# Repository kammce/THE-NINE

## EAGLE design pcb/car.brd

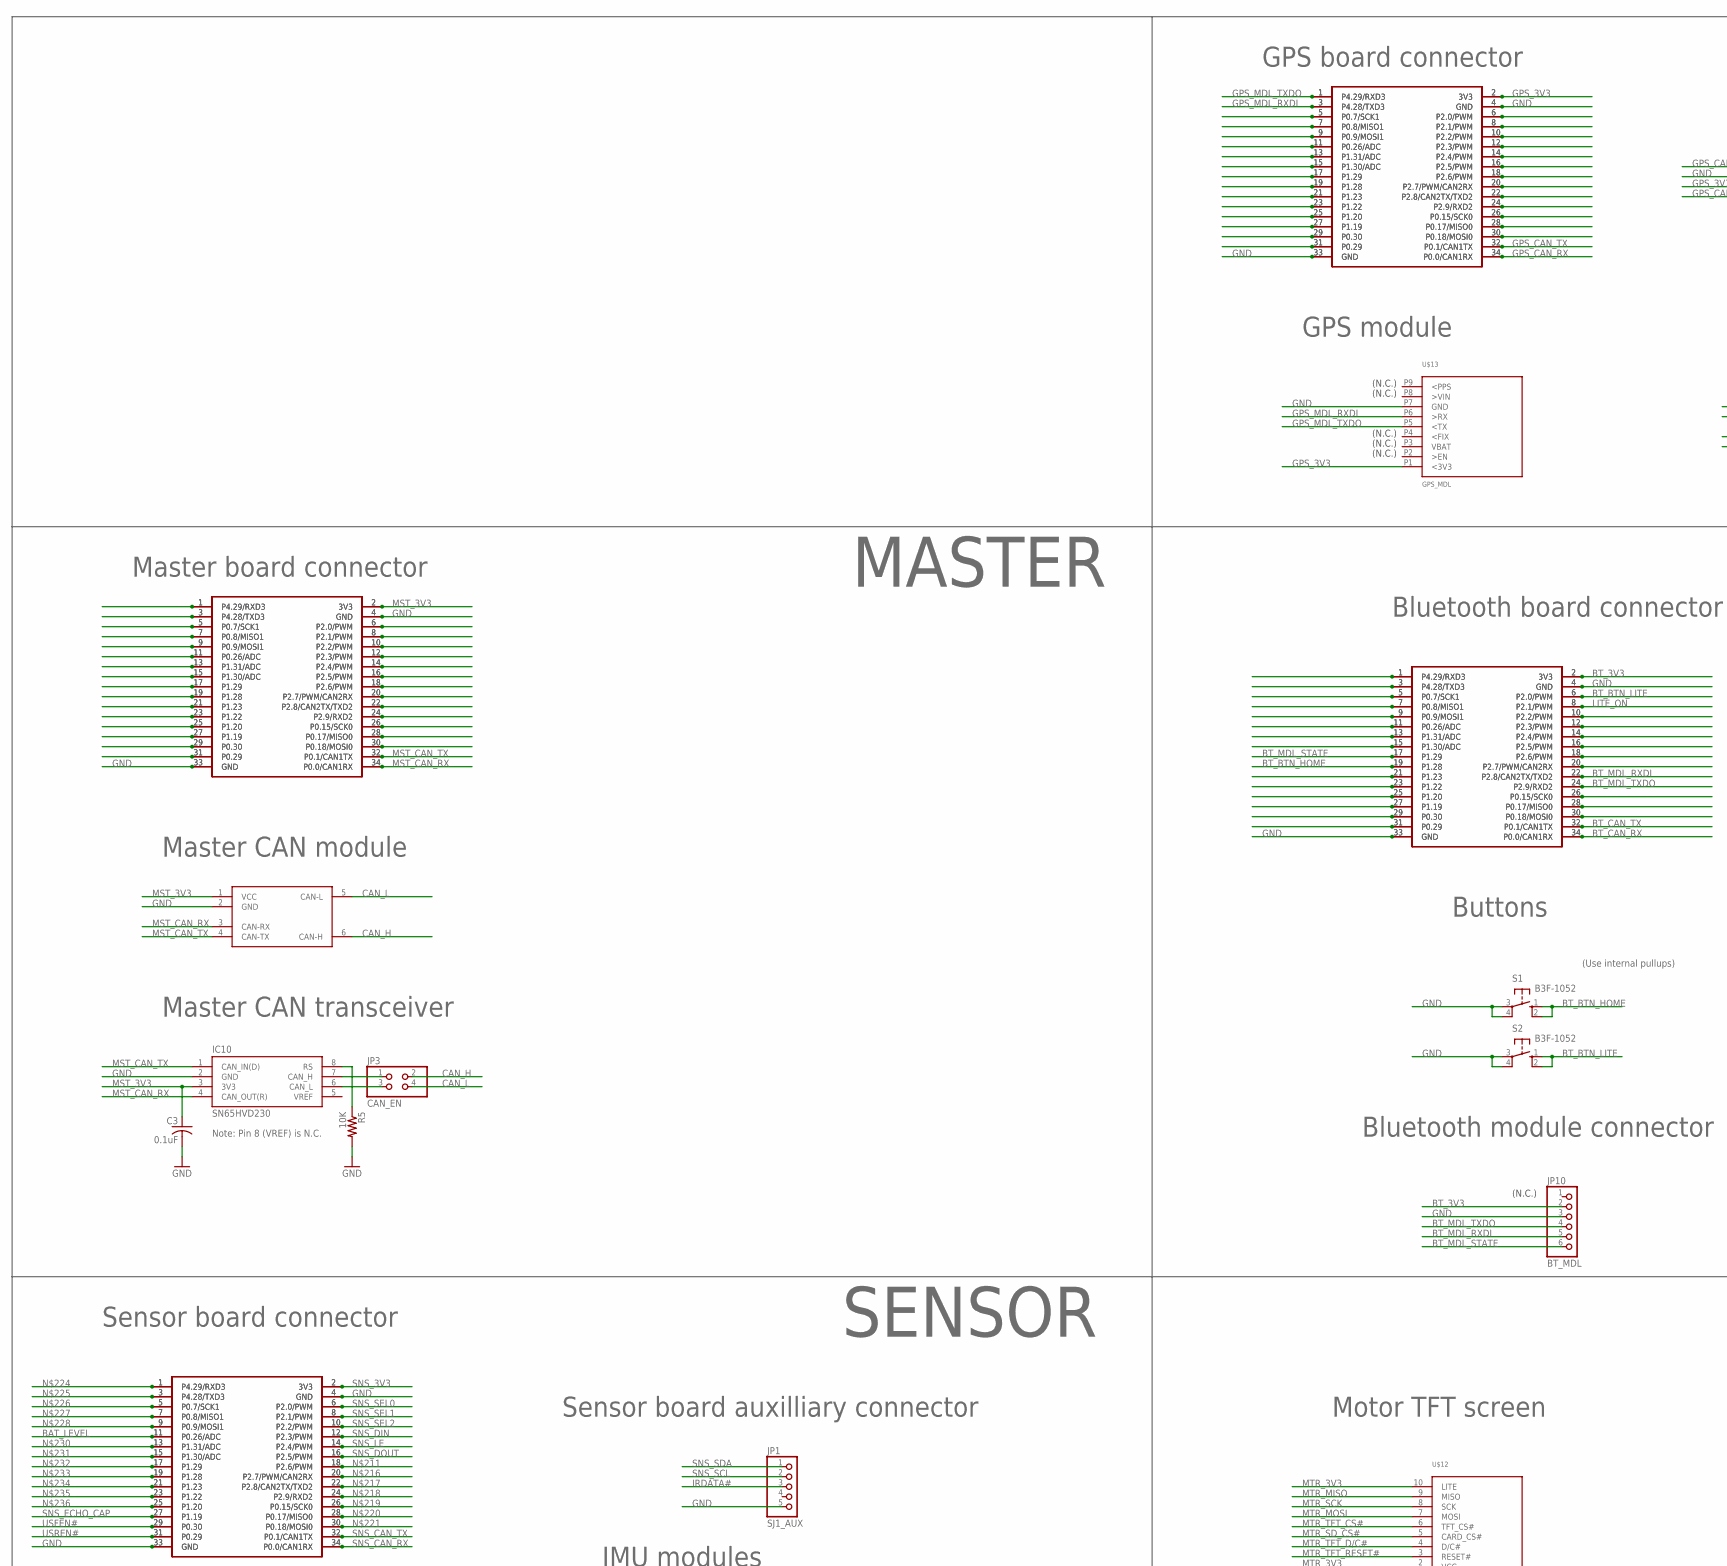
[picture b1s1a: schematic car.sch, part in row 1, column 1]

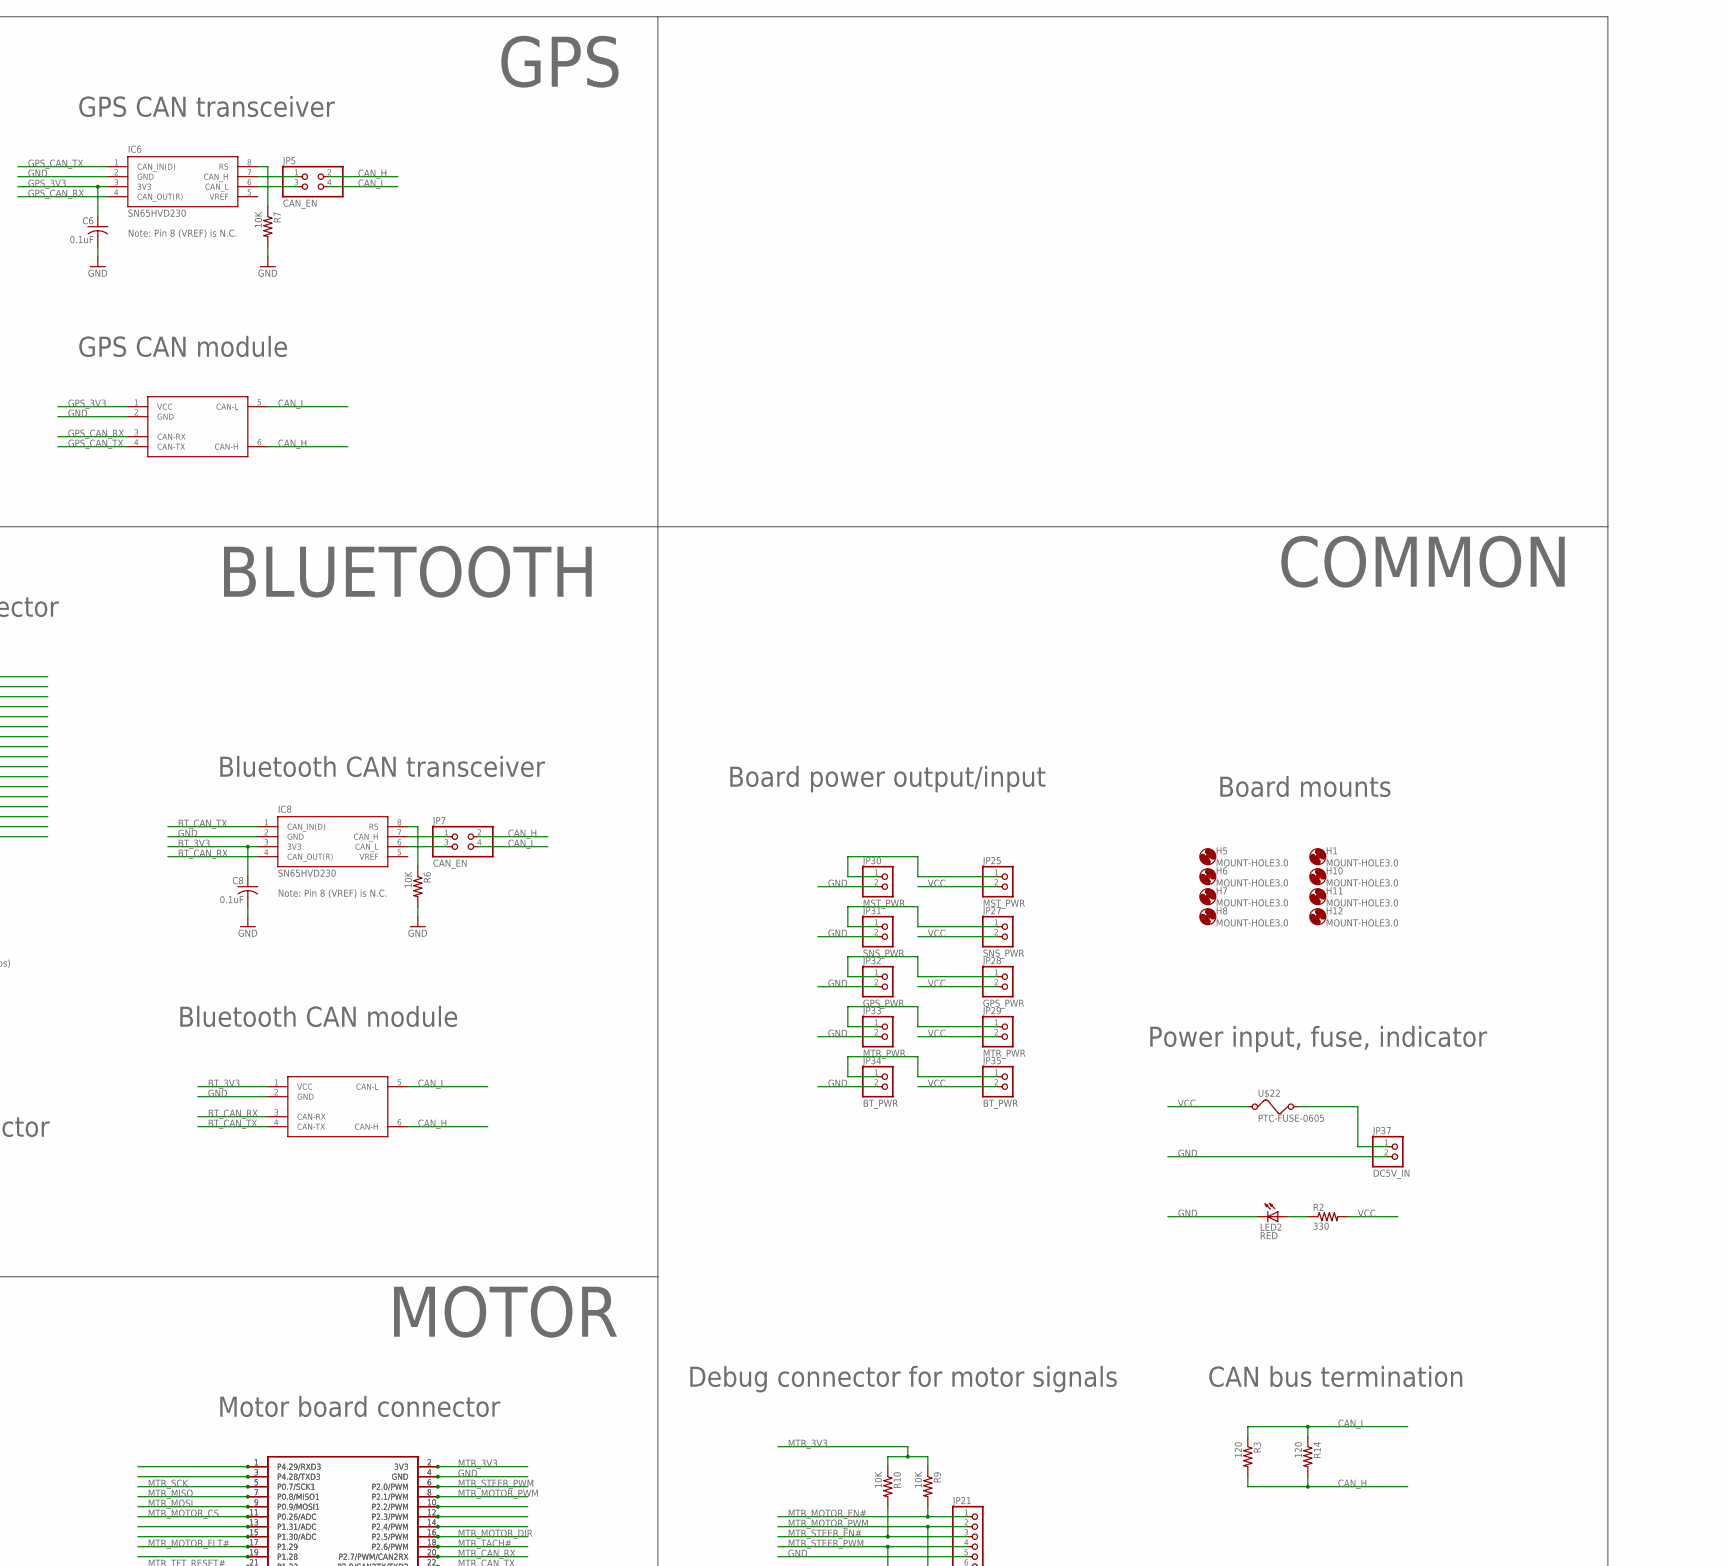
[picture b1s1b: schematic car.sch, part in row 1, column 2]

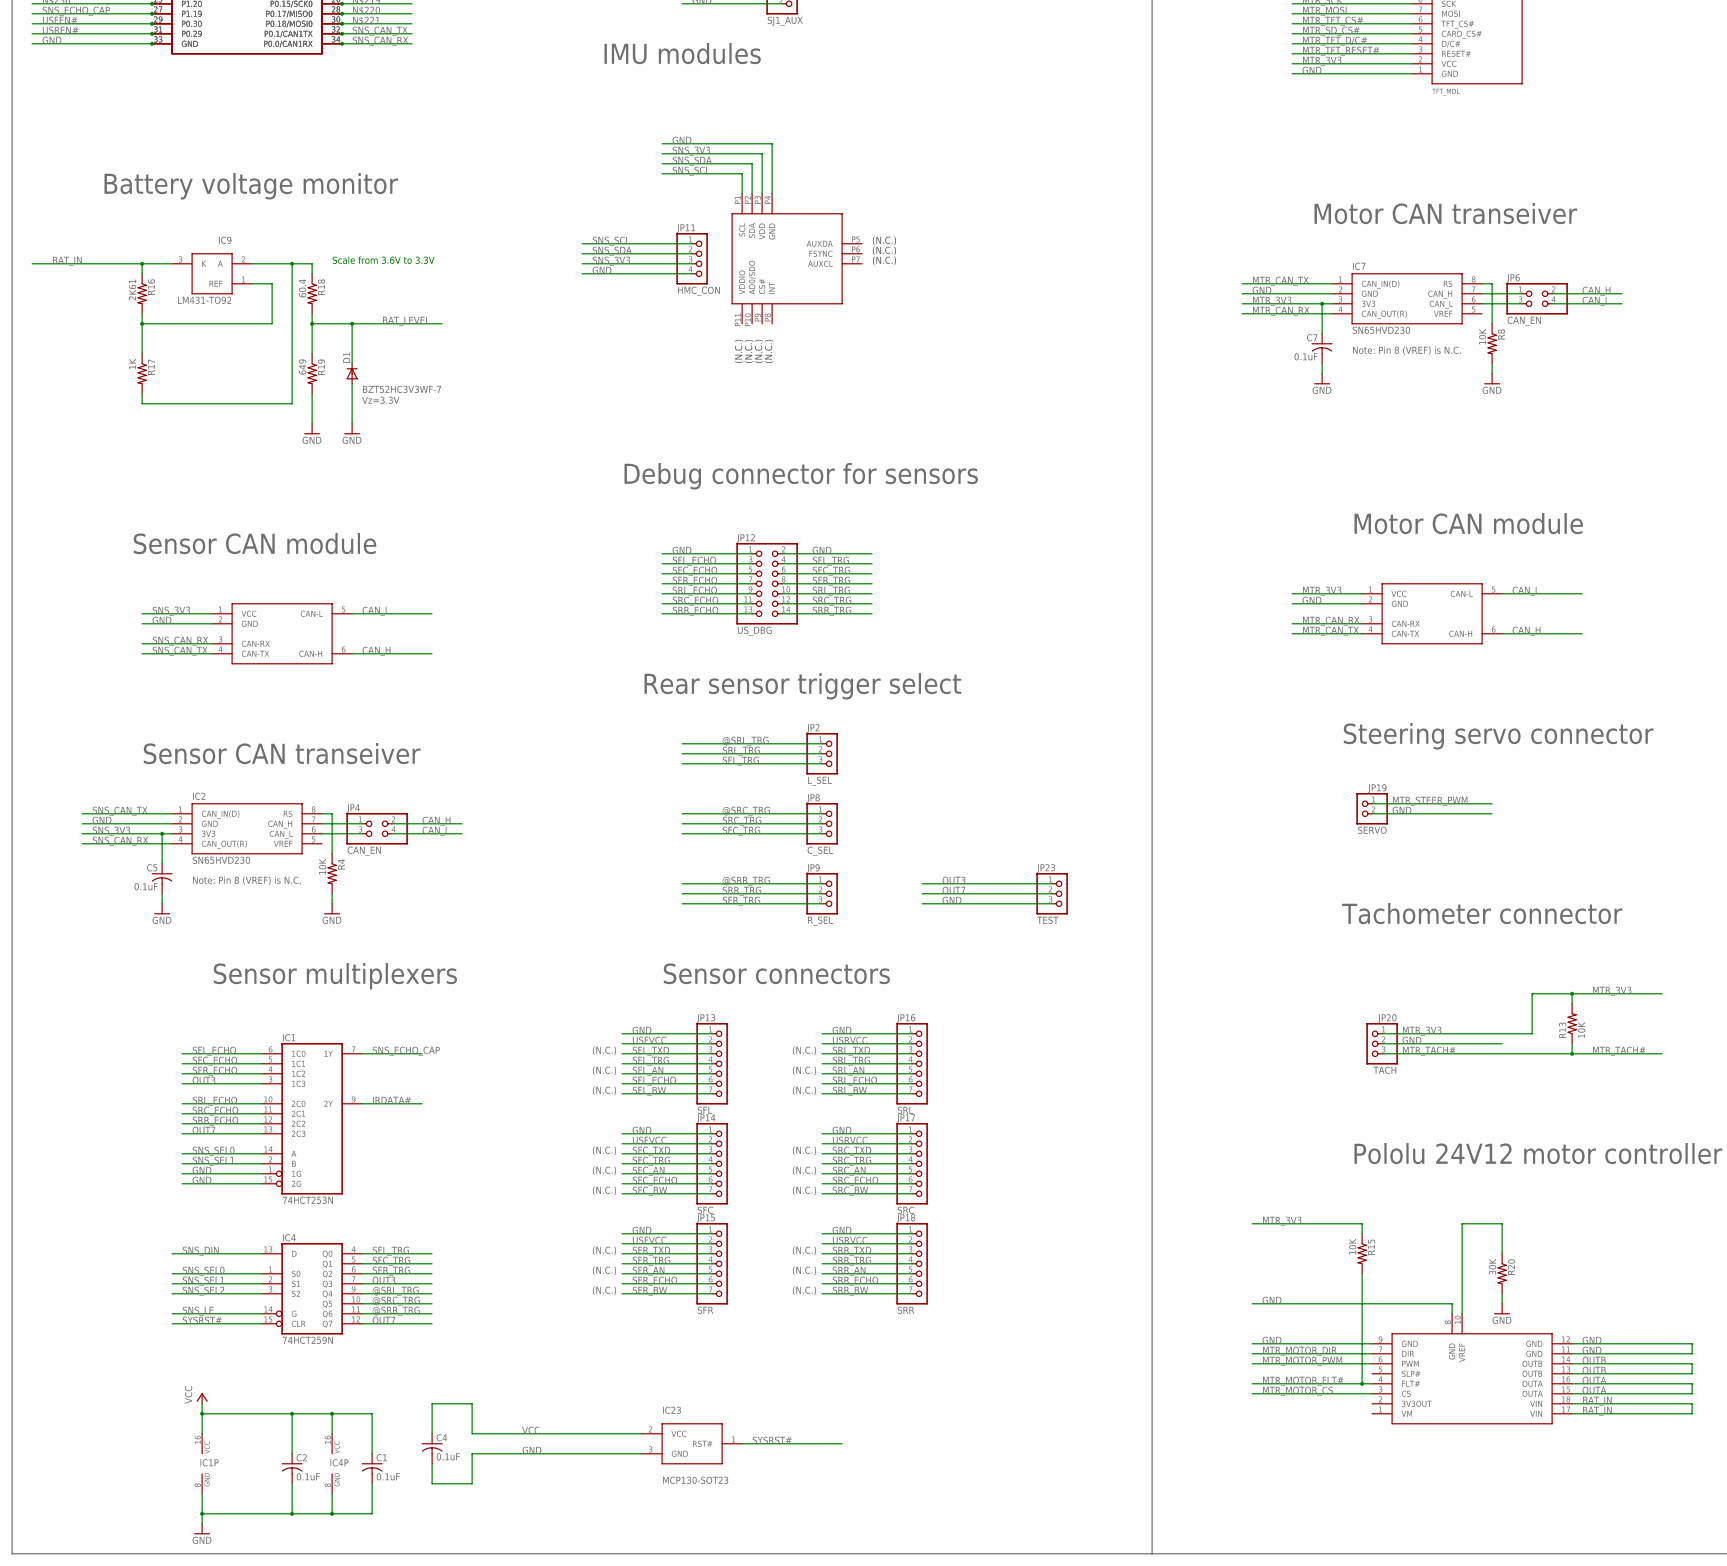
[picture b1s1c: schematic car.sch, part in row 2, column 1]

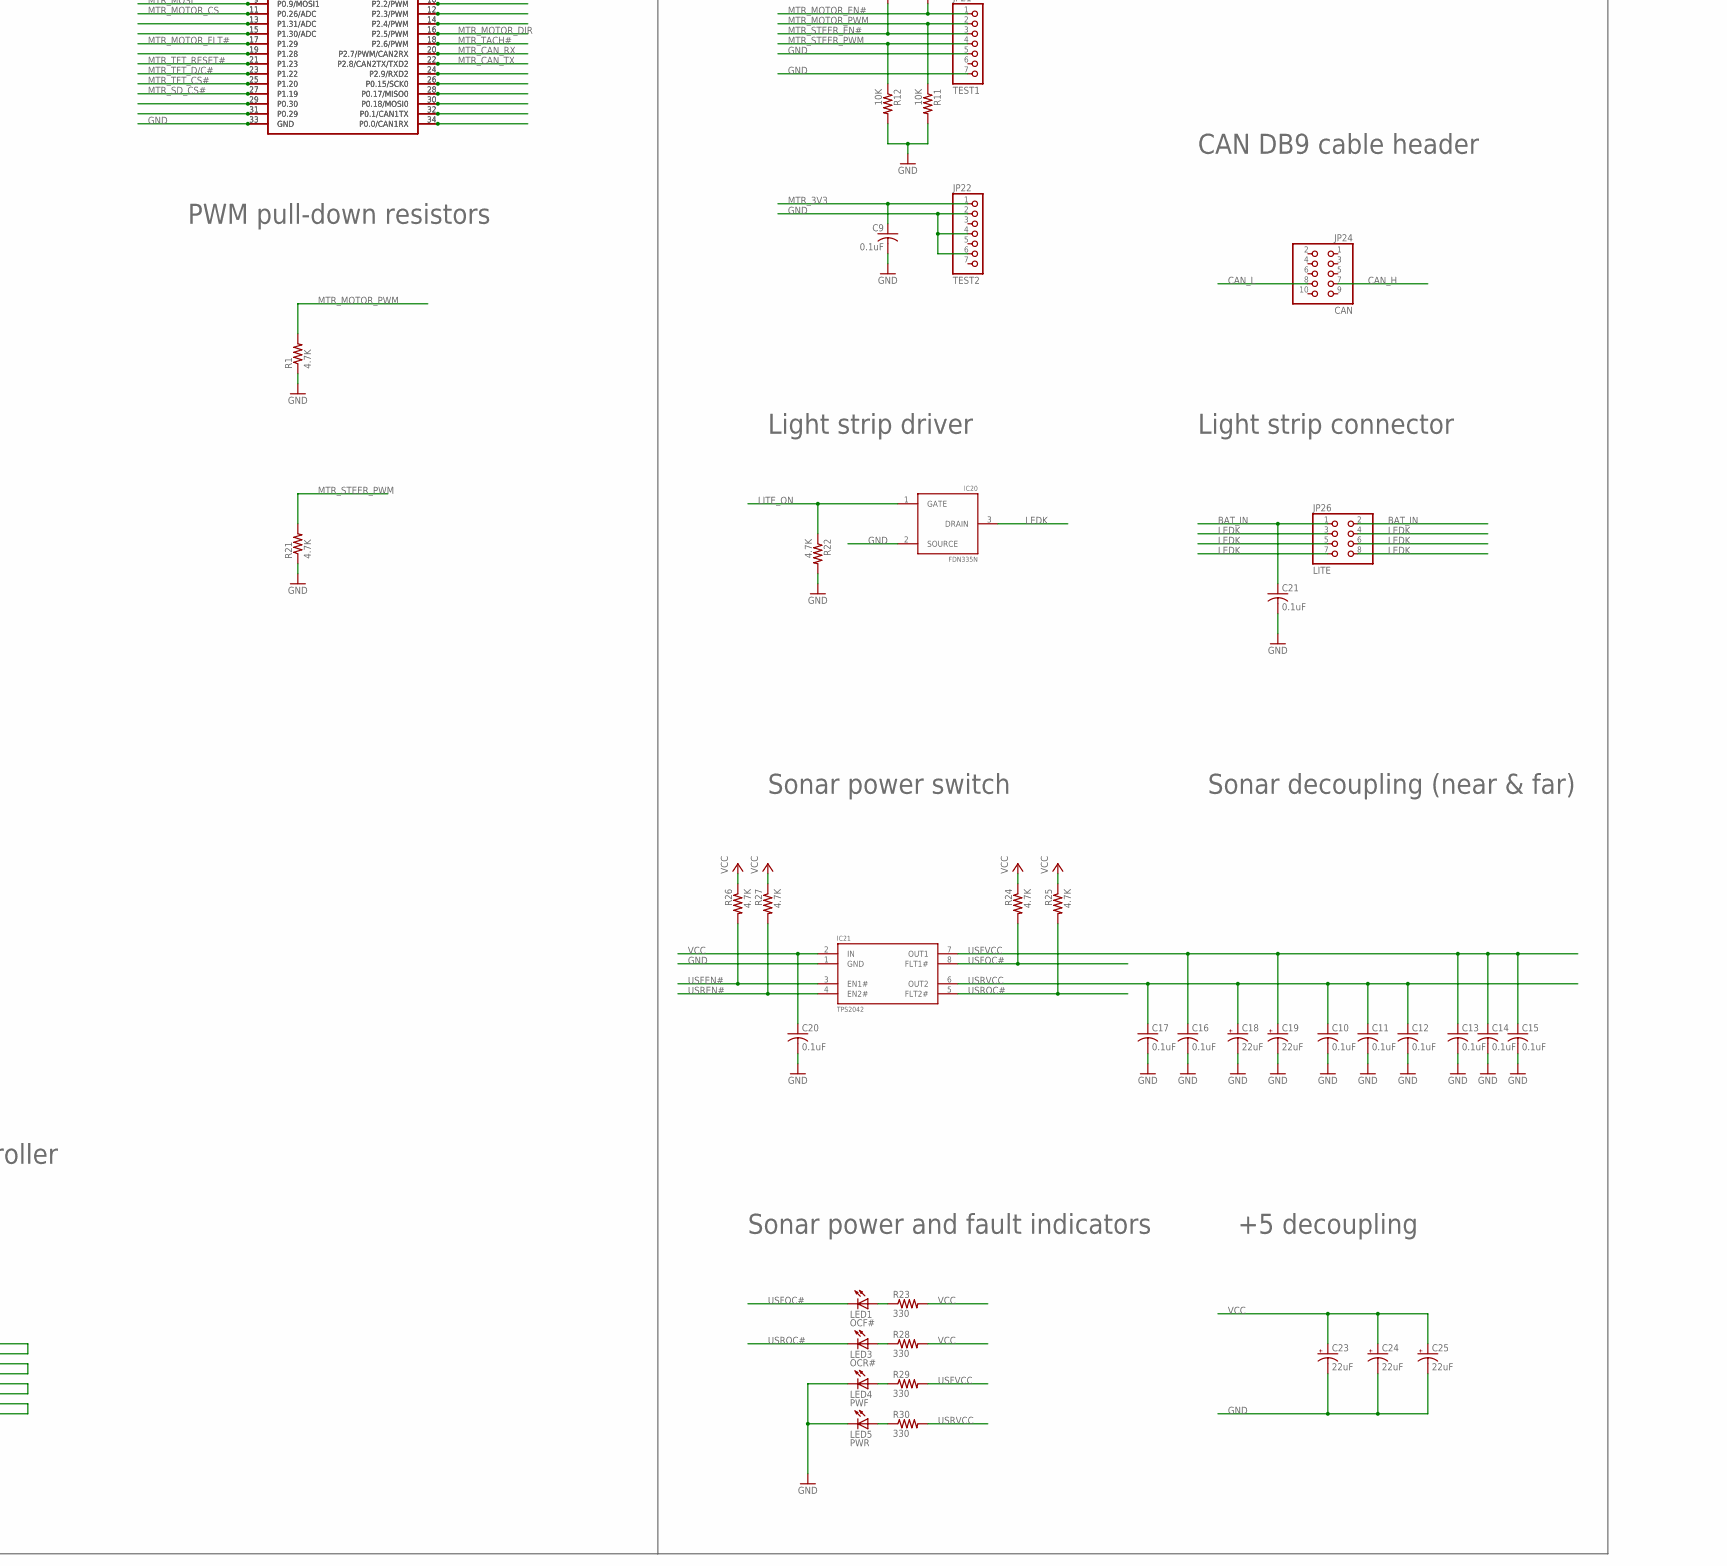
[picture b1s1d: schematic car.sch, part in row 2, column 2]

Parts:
C1, C2, C3, C4, C5, C6, C7, C8, C9, C10, C11, C12, C13, C14, C15, C16, C17, C20, C21: 0.1uF; C0603K
C18, C19, C23, C24, C25: 22uF; D/7343-31W
D1: BZT52HC3V3WF-7; SOD323-W
H1, H5, H6, H7, H8, H10, H11, H12: MOUNT-HOLE3.0; 3,0
IC1: 74HCT253N; DIL16
IC2, IC6, IC7, IC8, IC10: SN65HVD230; SOIC8
IC4: 74HCT259N; DIL16
IC9: LM431-TO92; TO-92
IC20: FDN335N; SOT23-3
IC21: TPS2042; SOIC8
IC22: 24V21
IC23: MCP130-SOT23; SOT23-3
IMU_MDL: MPU9250
JP1: SJ1_AUX; 1X05
JP2: L_SEL; 1X03
JP3, JP4, JP5, JP6, JP7: CAN_EN; 2X02
JP8: C_SEL; 1X03
JP9: R_SEL; 1X03
JP10: BT_MDL; 1X06
JP11: HMC_CON; 1X04
JP12: US_DBG; 2X07
JP13: SFL; 1X07
JP14: SFC; 1X07
JP15: SFR; 1X07
JP16: SRL; 1X07
JP17: SRC; 1X07
JP18: SRR; 1X07
JP19: SERVO; 1X02
JP20: TACH; 1X03
JP21: TEST1; 1X07
JP22: TEST2; 1X07
JP23: TEST; 1X03
JP24: CAN; 2X05
JP25, JP30: MST_PWR; 1X02
JP26: LITE; 2X04
JP27, JP31: SNS_PWR; 1X02
JP28, JP32: GPS_PWR; 1X02
JP29, JP33: MTR_PWR; 1X02
JP34, JP35: BT_PWR; 1X02
JP37: DC5V_IN; 1X02
LED1: OCF#; CHIPLED_0603
LED2: RED; CHIPLED_0603
LED3: OCR#; CHIPLED_0603
LED4: PWF; CHIPLED_0603
LED5: PWR; CHIPLED_0603
R1, R21, R22, R24, R25, R26, R27: 4.7K; R0603
R2, R23, R28, R29, R30: 330; R0603
R3, R14: 120; R0603
R4, R5, R6, R7, R8, R9, R10, R11, R12, R13, R15: 10K; R0603
R16: 2K61; R0603
R17: 1K; R0603
R18: 60.4; R0603
R19: 649; R0603
R20: 30K; R0603
S1, S2: B3F-1052; B3F-10XX
U$7, U$8, U$9, U$10, U$11: WAVESHARE-CAN
U$12: TFT_MDL; ADA-TFT
U$13: GPS_MDL; ADA-GPS
U$19, U$20, U$23, U$24, U$25, U$26, U$27, U$28, U$29, U$30: SJ1_CONN
U$22: PTC-FUSE-0605; R0605

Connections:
@CAN_H: IC10.7 (CAN_H), JP3.1
@CAN_H1: IC2.7 (CAN_H), JP4.1
@CAN_H2: IC6.7 (CAN_H), JP5.1
@CAN_H3: IC7.7 (CAN_H), JP6.1
@CAN_H4: IC8.7 (CAN_H), JP7.1
@CAN_L: IC10.6 (CAN_L), JP3.3
@CAN_L1: IC2.6 (CAN_L), JP4.3
@CAN_L2: IC6.6 (CAN_L), JP5.3
@CAN_L3: IC7.6 (CAN_L), JP6.3
@CAN_L4: IC8.6 (CAN_L), JP7.3
@SRC_TRG: IC4.10 (Q5), JP8.1
@SRL_TRG: IC4.9 (Q4), JP2.1
@SRR_TRG: IC4.11 (Q6), JP9.1
BAT_IN: C21.1, IC9.3 (K), IC22.17 (VIN), IC22.18 (VIN), JP26.1, JP26.2, R16.1
BAT_LEVEL: D1.C, R18.2, R19.1, U$19.11 (P0.26/ADC), U$20.11 (P0.26/ADC)
BT_3V3: C8.1, IC8.3 (3V3), JP10.2, U$8.1 (VCC), U$27.2 (3V3), U$30.2 (3V3)
BT_BTN_HOME: S1.1 (S), S1.2 (S1), U$27.19 (P1.28), U$30.19 (P1.28)
BT_BTN_LITE: S2.1 (S), S2.2 (S1), U$27.6 (P2.0/PWM), U$30.6 (P2.0/PWM)
BT_CAN_RX: IC8.4 (CAN_OUT(R)), U$8.3 (CAN-RX), U$27.34 (P0.0/CAN1RX), U$30.34 (P0.0/CAN1RX)
BT_CAN_TX: IC8.1 (CAN_IN(D)), U$8.4 (CAN-TX), U$27.32 (P0.1/CAN1TX), U$30.32 (P0.1/CAN1TX)
BT_MDL_RXDI: JP10.5, U$27.22 (P2.8/CAN2TX/TXD2), U$30.22 (P2.8/CAN2TX/TXD2)
BT_MDL_STATE: JP10.6, U$27.17 (P1.29), U$30.17 (P1.29)
BT_MDL_TXDO: JP10.4, U$27.24 (P2.9/RXD2), U$30.24 (P2.9/RXD2)
CAN_H: JP3.2, JP4.2, JP5.2, JP6.2, JP7.2, JP24.7, R3.2, R14.2, U$7.6 (CAN-H), U$8.6 (CAN-H), U$9.6 (CAN-H), U$10.6 (CAN-H), U$11.6 (CAN-H)
CAN_L: JP3.4, JP4.4, JP5.4, JP6.4, JP7.4, JP24.8, R3.1, R14.1, U$7.5 (CAN-L), U$8.5 (CAN-L), U$9.5 (CAN-L), U$10.5 (CAN-L), U$11.5 (CAN-L)
EXT_VCC: JP37.1, U$22.2
GND: C1.2, C2.2, C3.2, C4.2, C5.2, C6.2, C7.2, C8.2, C9.2, C10.2, C11.2, C12.2, C13.2, C14.2, C15.2, C16.2, C17.2, C18.-, C19.-, C20.2, C21.2, C23.-, C24.-, C25.-, D1.A, IC1.1 (1G), IC1.8 (GND), IC1.15 (2G), IC2.2 (GND), IC4.8 (GND), IC6.2 (GND), IC7.2 (GND), IC8.2 (GND), IC10.2 (GND), IC20.2 (SOURCE), IC21.1 (GND), IC22.8 (GND), IC22.9 (GND), IC22.11 (GND), IC22.12 (GND), IC23.3 (GND), IMU_MDL.P4 (GND), JP1.5, JP10.3, JP11.4, JP12.1, JP12.2, JP13.1, JP14.1, JP15.1, JP16.1, JP17.1, JP18.1, JP19.2, JP20.2, JP21.5, JP21.7, JP22.2, JP22.4, JP22.6, JP23.3, JP30.2, JP31.2, JP32.2, JP33.2, JP34.2, JP37.2, LED2.C, LED4.C, LED5.C, R1.1, R4.2, R5.2, R6.2, R7.2, R8.2, R11.2, R12.2, R19.2, R20.2, R21.1, R22.2, S1.3, S1.4 (P1), S2.3, S2.4 (P1), U$7.2 (GND), U$8.2 (GND), U$9.2 (GND), U$10.2 (GND), U$11.2 (GND), U$12.1 (GND), U$13.P7 (GND), U$19.4 (GND), U$19.33 (GND), U$20.4 (GND), U$20.33 (GND), U$23.4 (GND), U$23.33 (GND), U$24.4 (GND), U$24.33 (GND), U$25.4 (GND), U$25.33 (GND), U$26.4 (GND), U$26.33 (GND), U$27.4 (GND), U$27.33 (GND), U$28.4 (GND), U$28.33 (GND), U$29.4 (GND), U$29.33 (GND), U$30.4 (GND), U$30.33 (GND)
GPS_3V3: C6.1, IC6.3 (3V3), U$10.1 (VCC), U$13.P1 (<3V3), U$28.2 (3V3), U$29.2 (3V3)
GPS_CAN_RX: IC6.4 (CAN_OUT(R)), U$10.3 (CAN-RX), U$28.34 (P0.0/CAN1RX), U$29.34 (P0.0/CAN1RX)
GPS_CAN_TX: IC6.1 (CAN_IN(D)), U$10.4 (CAN-TX), U$28.32 (P0.1/CAN1TX), U$29.32 (P0.1/CAN1TX)
GPS_MDL_RXDI: U$13.P6 (>RX), U$28.3 (P4.28/TXD3), U$29.3 (P4.28/TXD3)
GPS_MDL_TXDO: U$13.P5 (<TX), U$28.1 (P4.29/RXD3), U$29.1 (P4.29/RXD3)
IRDATA#: IC1.9 (2Y), JP1.3
LEDK: IC20.3 (DRAIN), JP26.3, JP26.4, JP26.5, JP26.6, JP26.7, JP26.8
LITE_ON: IC20.1 (GATE), R22.1, U$27.8 (P2.1/PWM), U$30.8 (P2.1/PWM)
MST_3V3: C3.1, IC10.3 (3V3), U$7.1 (VCC), U$23.2 (3V3), U$24.2 (3V3)
MST_CAN_RX: IC10.4 (CAN_OUT(R)), U$7.3 (CAN-RX), U$23.34 (P0.0/CAN1RX), U$24.34 (P0.0/CAN1RX)
MST_CAN_TX: IC10.1 (CAN_IN(D)), U$7.4 (CAN-TX), U$23.32 (P0.1/CAN1TX), U$24.32 (P0.1/CAN1TX)
MTR_3V3: C7.1, C9.1, IC7.3 (3V3), JP20.1, JP22.1, R9.1, R10.1, R13.2, R15.1, U$11.1 (VCC), U$12.2 (VCC), U$12.10 (LITE), U$25.2 (3V3), U$26.2 (3V3)
MTR_CAN_RX: IC7.4 (CAN_OUT(R)), U$11.3 (CAN-RX), U$25.20 (P2.7/PWM/CAN2RX), U$26.20 (P2.7/PWM/CAN2RX)
MTR_CAN_TX: IC7.1 (CAN_IN(D)), U$11.4 (CAN-TX), U$25.22 (P2.8/CAN2TX/TXD2), U$26.22 (P2.8/CAN2TX/TXD2)
MTR_MISO: U$12.9 (MISO), U$25.7 (P0.8/MISO1), U$26.7 (P0.8/MISO1)
MTR_MOSI: U$12.7 (MOSI), U$25.9 (P0.9/MOSI1), U$26.9 (P0.9/MOSI1)
MTR_MOTOR_CS: IC22.3 (CS), U$25.11 (P0.26/ADC), U$26.11 (P0.26/ADC)
MTR_MOTOR_DIR: IC22.7 (DIR), U$25.16 (P2.5/PWM), U$26.16 (P2.5/PWM)
MTR_MOTOR_EN#: JP21.1, R9.2, U$25.14 (P2.4/PWM), U$26.14 (P2.4/PWM)
MTR_MOTOR_FLT#: IC22.4 (FLT#), R15.2, U$25.17 (P1.29), U$26.17 (P1.29)
MTR_MOTOR_PWM: IC22.6 (PWM), JP21.2, R1.2, R11.1, U$25.8 (P2.1/PWM), U$26.8 (P2.1/PWM)
MTR_SCK: U$12.8 (SCK), U$25.5 (P0.7/SCK1), U$26.5 (P0.7/SCK1)
MTR_SD_CS#: U$12.5 (CARD_CS#), U$25.27 (P1.19), U$26.27 (P1.19)
MTR_STEER_EN#: JP21.3, R10.2, U$25.12 (P2.3/PWM), U$26.12 (P2.3/PWM)
MTR_STEER_PWM: JP19.1, JP21.4, R12.1, R21.2, U$25.6 (P2.0/PWM), U$26.6 (P2.0/PWM)
MTR_TACH#: JP20.3, R13.1, U$25.18 (P2.6/PWM), U$26.18 (P2.6/PWM)
MTR_TFT_CS#: U$12.6 (TFT_CS#), U$25.25 (P1.20), U$26.25 (P1.20)
MTR_TFT_D/C#: U$12.4 (D/C#), U$25.23 (P1.22), U$26.23 (P1.22)
MTR_TFT_RESET#: U$12.3 (RESET#), U$25.21 (P1.23), U$26.21 (P1.23)
unnamed: IC10.8 (RS), R5.1
unnamed: IC2.8 (RS), R4.1
unnamed: IC6.8 (RS), R7.1
unnamed: IC7.8 (RS), R8.1
unnamed: IC8.8 (RS), R6.1
unnamed: LED2.A, R2.1
unnamed: IC22.10 (VREF), R20.1
unnamed: LED1.A, R23.1
unnamed: LED3.A, R28.1
unnamed: LED4.A, R29.1
unnamed: LED5.A, R30.1
unnamed: IC9.2 (A), R17.2, R18.1
unnamed: JP34.1, JP35.1
unnamed: U$25.1 (P4.29/RXD3), U$26.1 (P4.29/RXD3)
unnamed: U$25.3 (P4.28/TXD3), U$26.3 (P4.28/TXD3)
unnamed: JP29.1, JP33.1
unnamed: JP28.1, JP32.1
unnamed: JP27.1, JP31.1
unnamed: JP25.1, JP30.1
unnamed: U$25.13 (P1.31/ADC), U$26.13 (P1.31/ADC)
unnamed: U$25.15 (P1.30/ADC), U$26.15 (P1.30/ADC)
unnamed: U$25.19 (P1.28), U$26.19 (P1.28)
unnamed: U$25.29 (P0.30), U$26.29 (P0.30)
unnamed: U$25.31 (P0.29), U$26.31 (P0.29)
unnamed: U$27.1 (P4.29/RXD3), U$30.1 (P4.29/RXD3)
unnamed: U$27.3 (P4.28/TXD3), U$30.3 (P4.28/TXD3)
unnamed: U$27.5 (P0.7/SCK1), U$30.5 (P0.7/SCK1)
unnamed: U$25.10 (P2.2/PWM), U$26.10 (P2.2/PWM)
unnamed: U$25.24 (P2.9/RXD2), U$26.24 (P2.9/RXD2)
unnamed: U$25.26 (P0.15/SCK0), U$26.26 (P0.15/SCK0)
unnamed: U$25.28 (P0.17/MISO0), U$26.28 (P0.17/MISO0)
unnamed: U$25.30 (P0.18/MOSI0), U$26.30 (P0.18/MOSI0)
unnamed: U$25.32 (P0.1/CAN1TX), U$26.32 (P0.1/CAN1TX)
unnamed: U$25.34 (P0.0/CAN1RX), U$26.34 (P0.0/CAN1RX)
unnamed: U$27.7 (P0.8/MISO1), U$30.7 (P0.8/MISO1)
unnamed: U$27.9 (P0.9/MOSI1), U$30.9 (P0.9/MOSI1)
unnamed: U$27.11 (P0.26/ADC), U$30.11 (P0.26/ADC)
unnamed: U$27.13 (P1.31/ADC), U$30.13 (P1.31/ADC)
unnamed: U$27.15 (P1.30/ADC), U$30.15 (P1.30/ADC)
unnamed: U$27.21 (P1.23), U$30.21 (P1.23)
unnamed: U$27.23 (P1.22), U$30.23 (P1.22)
unnamed: U$27.25 (P1.20), U$30.25 (P1.20)
unnamed: U$27.27 (P1.19), U$30.27 (P1.19)
unnamed: U$27.29 (P0.30), U$30.29 (P0.30)
unnamed: U$27.31 (P0.29), U$30.31 (P0.29)
unnamed: U$27.10 (P2.2/PWM), U$30.10 (P2.2/PWM)
unnamed: U$27.12 (P2.3/PWM), U$30.12 (P2.3/PWM)
unnamed: U$27.14 (P2.4/PWM), U$30.14 (P2.4/PWM)
unnamed: U$27.16 (P2.5/PWM), U$30.16 (P2.5/PWM)
unnamed: U$27.18 (P2.6/PWM), U$30.18 (P2.6/PWM)
unnamed: U$27.20 (P2.7/PWM/CAN2RX), U$30.20 (P2.7/PWM/CAN2RX)
unnamed: IC9.1 (REF), R16.2, R17.1
unnamed: U$23.1 (P4.29/RXD3), U$24.1 (P4.29/RXD3)
unnamed: U$23.3 (P4.28/TXD3), U$24.3 (P4.28/TXD3)
unnamed: U$23.5 (P0.7/SCK1), U$24.5 (P0.7/SCK1)
unnamed: U$23.7 (P0.8/MISO1), U$24.7 (P0.8/MISO1)
unnamed: U$19.18 (P2.6/PWM), U$20.18 (P2.6/PWM)
unnamed: U$19.20 (P2.7/PWM/CAN2RX), U$20.20 (P2.7/PWM/CAN2RX)
unnamed: U$19.22 (P2.8/CAN2TX/TXD2), U$20.22 (P2.8/CAN2TX/TXD2)
unnamed: U$19.24 (P2.9/RXD2), U$20.24 (P2.9/RXD2)
unnamed: U$19.26 (P0.15/SCK0), U$20.26 (P0.15/SCK0)
unnamed: U$19.28 (P0.17/MISO0), U$20.28 (P0.17/MISO0)
unnamed: U$19.30 (P0.18/MOSI0), U$20.30 (P0.18/MOSI0)
unnamed: U$19.1 (P4.29/RXD3), U$20.1 (P4.29/RXD3)
unnamed: U$19.3 (P4.28/TXD3), U$20.3 (P4.28/TXD3)
unnamed: U$19.5 (P0.7/SCK1), U$20.5 (P0.7/SCK1)
unnamed: U$19.7 (P0.8/MISO1), U$20.7 (P0.8/MISO1)
unnamed: U$19.9 (P0.9/MOSI1), U$20.9 (P0.9/MOSI1)
unnamed: U$19.13 (P1.31/ADC), U$20.13 (P1.31/ADC)
unnamed: U$19.15 (P1.30/ADC), U$20.15 (P1.30/ADC)
unnamed: U$19.17 (P1.29), U$20.17 (P1.29)
unnamed: U$19.19 (P1.28), U$20.19 (P1.28)
unnamed: U$19.21 (P1.23), U$20.21 (P1.23)
unnamed: U$19.23 (P1.22), U$20.23 (P1.22)
unnamed: U$19.25 (P1.20), U$20.25 (P1.20)
unnamed: U$23.9 (P0.9/MOSI1), U$24.9 (P0.9/MOSI1)
unnamed: U$23.11 (P0.26/ADC), U$24.11 (P0.26/ADC)
unnamed: U$23.13 (P1.31/ADC), U$24.13 (P1.31/ADC)
unnamed: U$23.15 (P1.30/ADC), U$24.15 (P1.30/ADC)
unnamed: U$23.17 (P1.29), U$24.17 (P1.29)
unnamed: U$23.19 (P1.28), U$24.19 (P1.28)
unnamed: U$23.21 (P1.23), U$24.21 (P1.23)
unnamed: U$23.23 (P1.22), U$24.23 (P1.22)
unnamed: U$23.25 (P1.20), U$24.25 (P1.20)
unnamed: U$23.27 (P1.19), U$24.27 (P1.19)
unnamed: U$23.29 (P0.30), U$24.29 (P0.30)
unnamed: U$23.31 (P0.29), U$24.31 (P0.29)
unnamed: U$27.26 (P0.15/SCK0), U$30.26 (P0.15/SCK0)
unnamed: U$27.28 (P0.17/MISO0), U$30.28 (P0.17/MISO0)
unnamed: U$27.30 (P0.18/MOSI0), U$30.30 (P0.18/MOSI0)
unnamed: U$23.6 (P2.0/PWM), U$24.6 (P2.0/PWM)
unnamed: U$23.8 (P2.1/PWM), U$24.8 (P2.1/PWM)
unnamed: U$23.10 (P2.2/PWM), U$24.10 (P2.2/PWM)
unnamed: U$23.12 (P2.3/PWM), U$24.12 (P2.3/PWM)
unnamed: U$23.14 (P2.4/PWM), U$24.14 (P2.4/PWM)
unnamed: U$23.16 (P2.5/PWM), U$24.16 (P2.5/PWM)
unnamed: U$23.18 (P2.6/PWM), U$24.18 (P2.6/PWM)
unnamed: U$23.20 (P2.7/PWM/CAN2RX), U$24.20 (P2.7/PWM/CAN2RX)
unnamed: U$23.22 (P2.8/CAN2TX/TXD2), U$24.22 (P2.8/CAN2TX/TXD2)
unnamed: U$23.24 (P2.9/RXD2), U$24.24 (P2.9/RXD2)
unnamed: U$23.26 (P0.15/SCK0), U$24.26 (P0.15/SCK0)
unnamed: U$23.28 (P0.17/MISO0), U$24.28 (P0.17/MISO0)
unnamed: U$23.30 (P0.18/MOSI0), U$24.30 (P0.18/MOSI0)
unnamed: U$28.5 (P0.7/SCK1), U$29.5 (P0.7/SCK1)
unnamed: U$28.7 (P0.8/MISO1), U$29.7 (P0.8/MISO1)
unnamed: U$28.9 (P0.9/MOSI1), U$29.9 (P0.9/MOSI1)
unnamed: U$28.11 (P0.26/ADC), U$29.11 (P0.26/ADC)
unnamed: U$28.13 (P1.31/ADC), U$29.13 (P1.31/ADC)
unnamed: U$28.15 (P1.30/ADC), U$29.15 (P1.30/ADC)
unnamed: U$28.17 (P1.29), U$29.17 (P1.29)
unnamed: U$28.19 (P1.28), U$29.19 (P1.28)
unnamed: U$28.21 (P1.23), U$29.21 (P1.23)
unnamed: U$28.23 (P1.22), U$29.23 (P1.22)
unnamed: U$28.25 (P1.20), U$29.25 (P1.20)
unnamed: U$28.27 (P1.19), U$29.27 (P1.19)
unnamed: U$28.29 (P0.30), U$29.29 (P0.30)
unnamed: U$28.31 (P0.29), U$29.31 (P0.29)
unnamed: U$28.6 (P2.0/PWM), U$29.6 (P2.0/PWM)
unnamed: U$28.8 (P2.1/PWM), U$29.8 (P2.1/PWM)
unnamed: U$28.10 (P2.2/PWM), U$29.10 (P2.2/PWM)
unnamed: U$28.12 (P2.3/PWM), U$29.12 (P2.3/PWM)
unnamed: U$28.14 (P2.4/PWM), U$29.14 (P2.4/PWM)
unnamed: U$28.16 (P2.5/PWM), U$29.16 (P2.5/PWM)
unnamed: U$28.18 (P2.6/PWM), U$29.18 (P2.6/PWM)
unnamed: U$28.20 (P2.7/PWM/CAN2RX), U$29.20 (P2.7/PWM/CAN2RX)
unnamed: U$28.22 (P2.8/CAN2TX/TXD2), U$29.22 (P2.8/CAN2TX/TXD2)
unnamed: U$28.24 (P2.9/RXD2), U$29.24 (P2.9/RXD2)
unnamed: U$28.26 (P0.15/SCK0), U$29.26 (P0.15/SCK0)
unnamed: U$28.28 (P0.17/MISO0), U$29.28 (P0.17/MISO0)
unnamed: U$28.30 (P0.18/MOSI0), U$29.30 (P0.18/MOSI0)
OUT3: IC1.3 (1C3), IC4.7 (Q3), JP23.1
OUT7: IC1.13 (2C3), IC4.12 (Q7), JP23.2
OUTA: IC22.15 (OUTA), IC22.16 (OUTA)
OUTB: IC22.13 (OUTB), IC22.14 (OUTB)
SFC_AN: JP14.5
SFC_BW: JP14.7
SFC_ECHO: IC1.5 (1C1), JP12.5, JP14.6
SFC_TRG: IC4.5 (Q1), JP8.3, JP12.6, JP14.4
SFC_TXD: JP14.3
SFL_AN: JP13.5
SFL_BW: JP13.7
SFL_ECHO: IC1.6 (1C0), JP12.3, JP13.6
SFL_TRG: IC4.4 (Q0), JP2.3, JP12.4, JP13.4
SFL_TXD: JP13.3
SFR_AN: JP15.5
SFR_BW: JP15.7
SFR_ECHO: IC1.4 (1C2), JP12.7, JP15.6
SFR_TRG: IC4.6 (Q2), JP9.3, JP12.8, JP15.4
SFR_TXD: JP15.3
SNS_3V3: C5.1, IC2.3 (3V3), IMU_MDL.P3 (VDD), JP11.3, U$9.1 (VCC), U$19.2 (3V3), U$20.2 (3V3)
SNS_CAN_RX: IC2.4 (CAN_OUT(R)), U$9.3 (CAN-RX), U$19.34 (P0.0/CAN1RX), U$20.34 (P0.0/CAN1RX)
SNS_CAN_TX: IC2.1 (CAN_IN(D)), U$9.4 (CAN-TX), U$19.32 (P0.1/CAN1TX), U$20.32 (P0.1/CAN1TX)
SNS_DIN: IC4.13 (D), U$19.12 (P2.3/PWM), U$20.12 (P2.3/PWM)
SNS_DOUT: U$19.16 (P2.5/PWM), U$20.16 (P2.5/PWM)
SNS_ECHO_CAP: IC1.7 (1Y), U$19.27 (P1.19), U$20.27 (P1.19)
SNS_LE: IC4.14 (G), U$19.14 (P2.4/PWM), U$20.14 (P2.4/PWM)
SNS_SCL: IMU_MDL.P1 (SCL), JP1.2, JP11.1
SNS_SDA: IMU_MDL.P2 (SDA), JP1.1, JP11.2
SNS_SEL0: IC1.14 (A), IC4.1 (S0), U$19.6 (P2.0/PWM), U$20.6 (P2.0/PWM)
SNS_SEL1: IC1.2 (B), IC4.2 (S1), U$19.8 (P2.1/PWM), U$20.8 (P2.1/PWM)
SNS_SEL2: IC4.3 (S2), U$19.10 (P2.2/PWM), U$20.10 (P2.2/PWM)
SRC_AN: JP17.5
SRC_BW: JP17.7
SRC_ECHO: IC1.11 (2C1), JP12.11, JP17.6
SRC_TRG: JP8.2, JP12.12, JP17.4
SRC_TXD: JP17.3
SRL_AN: JP16.5
SRL_BW: JP16.7
SRL_ECHO: IC1.10 (2C0), JP12.9, JP16.6
SRL_TRG: JP2.2, JP12.10, JP16.4
SRL_TXD: JP16.3
SRR_AN: JP18.5
SRR_BW: JP18.7
SRR_ECHO: IC1.12 (2C2), JP12.13, JP18.6
SRR_TRG: JP9.2, JP12.14, JP18.4
SRR_TXD: JP18.3
SYSRST#: IC4.15 (CLR), IC23.1 (RST#)
USFEN#: IC21.3 (EN1#), R26.2, U$19.29 (P0.30), U$20.29 (P0.30)
USFOC#: IC21.8 (FLT1#), LED1.C, R24.2
USFVCC: C13.1, C14.1, C15.1, C16.1, C19.+, IC21.7 (OUT1), JP13.2, JP14.2, JP15.2, R29.2
USREN#: IC21.4 (EN2#), R27.2, U$19.31 (P0.29), U$20.31 (P0.29)
USROC#: IC21.5 (FLT2#), LED3.C, R25.2
USRVCC: C10.1, C11.1, C12.1, C17.1, C18.+, IC21.6 (OUT2), JP16.2, JP17.2, JP18.2, R30.2
VCC: C1.1, C2.1, C4.1, C20.1, C23.+, C24.+, C25.+, IC1.16 (VCC), IC4.16 (VCC), IC21.2 (IN), IC23.2 (VCC), JP25.2, JP27.2, JP28.2, JP29.2, JP35.2, R2.2, R23.2, R24.1, R25.1, R26.1, R27.1, R28.2, U$22.1

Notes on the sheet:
PWM pull-down resistors
Sensor connectors
Sensor multiplexers
CAN DB9 cable header
(N.C.)
Board mounts
Tachometer connector
Steering servo connector
Sensor board connector
CAN bus termination
Pololu 24V12 motor controller
Scale from 3.6V to 3.3V
Vz=3.3V
Battery voltage monitor
Sensor board auxilliary connector
Sensor CAN module
Master board connector
Master CAN transceiver
Master CAN module
Motor CAN module
IMU modules
Motor TFT screen
Motor board connector
MASTER
SENSOR
MOTOR
GPS
BLUETOOTH
(Use internal pullups)
Board power output/input
COMMON
Note: Pin 8 (VREF) is N.C.
Sensor CAN transeiver
GPS CAN transceiver
Motor CAN transeiver
Bluetooth CAN transceiver
Debug connector for motor signals
Bluetooth board connector
GPS board connector
GPS module

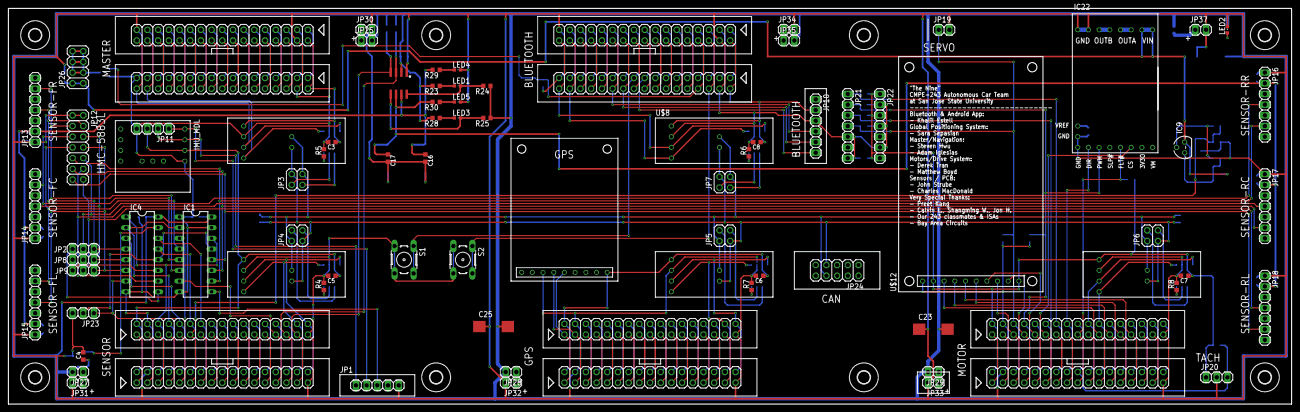
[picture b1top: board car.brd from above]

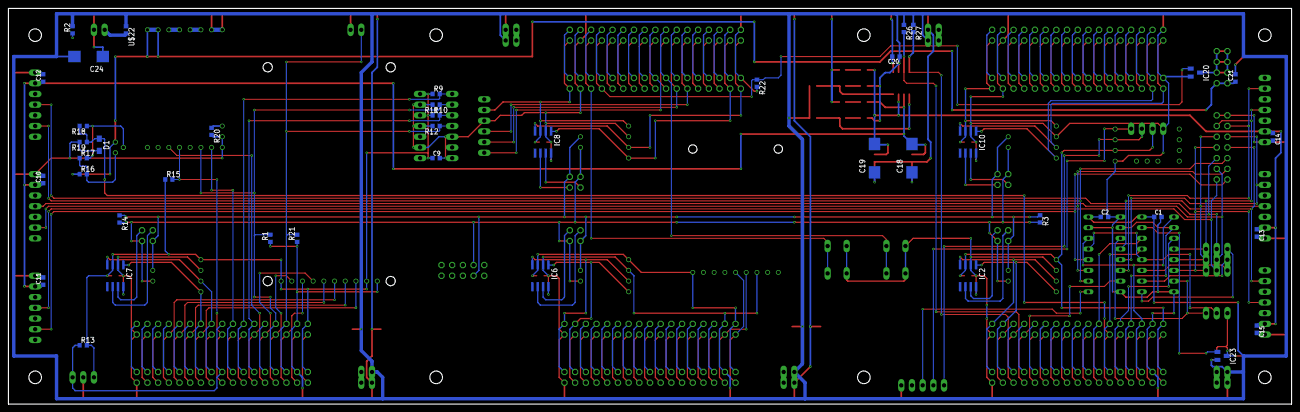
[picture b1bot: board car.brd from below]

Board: 2 copper layers, 304.8 x 94.0 mm, 137 parts (42 on the bottom side), 222 nets.

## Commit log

2017-06-30 Enhancement (#1)
    * Adding gdb-dashboard submodule to project
    * Reorganizing file structure
    * Removing ref_and_datasheets
    * Renamed projects to applications and the whole folder as a project and updated docs a bit. First setup of docs before real documentation
    * Fixing issue with .gitignore rules. needed to rename Firmware to firmware and delete files in firmware/default/obj
    * This should fail travis ci
2017-06-30 Changing travis.ci to master
2017-07-01 Adding content from CMPE 243 Course to github
2017-07-01 Adding rule to allow 'the-nine' folder to exist in .gitignore
2017-07-01 Made mistake... now the-nine folder should appear!
2017-07-01 Fixed issues with makefile
2017-07-08 adding high res app icon
2017-08-28 Adding updates to... stuff
2017-08-28 pruning repo and removing sensitive data
2017-12-20 Updated listeners file for the new bluetooth module
2018-02-04 Tuning for new long range sharp IR distance sensors
